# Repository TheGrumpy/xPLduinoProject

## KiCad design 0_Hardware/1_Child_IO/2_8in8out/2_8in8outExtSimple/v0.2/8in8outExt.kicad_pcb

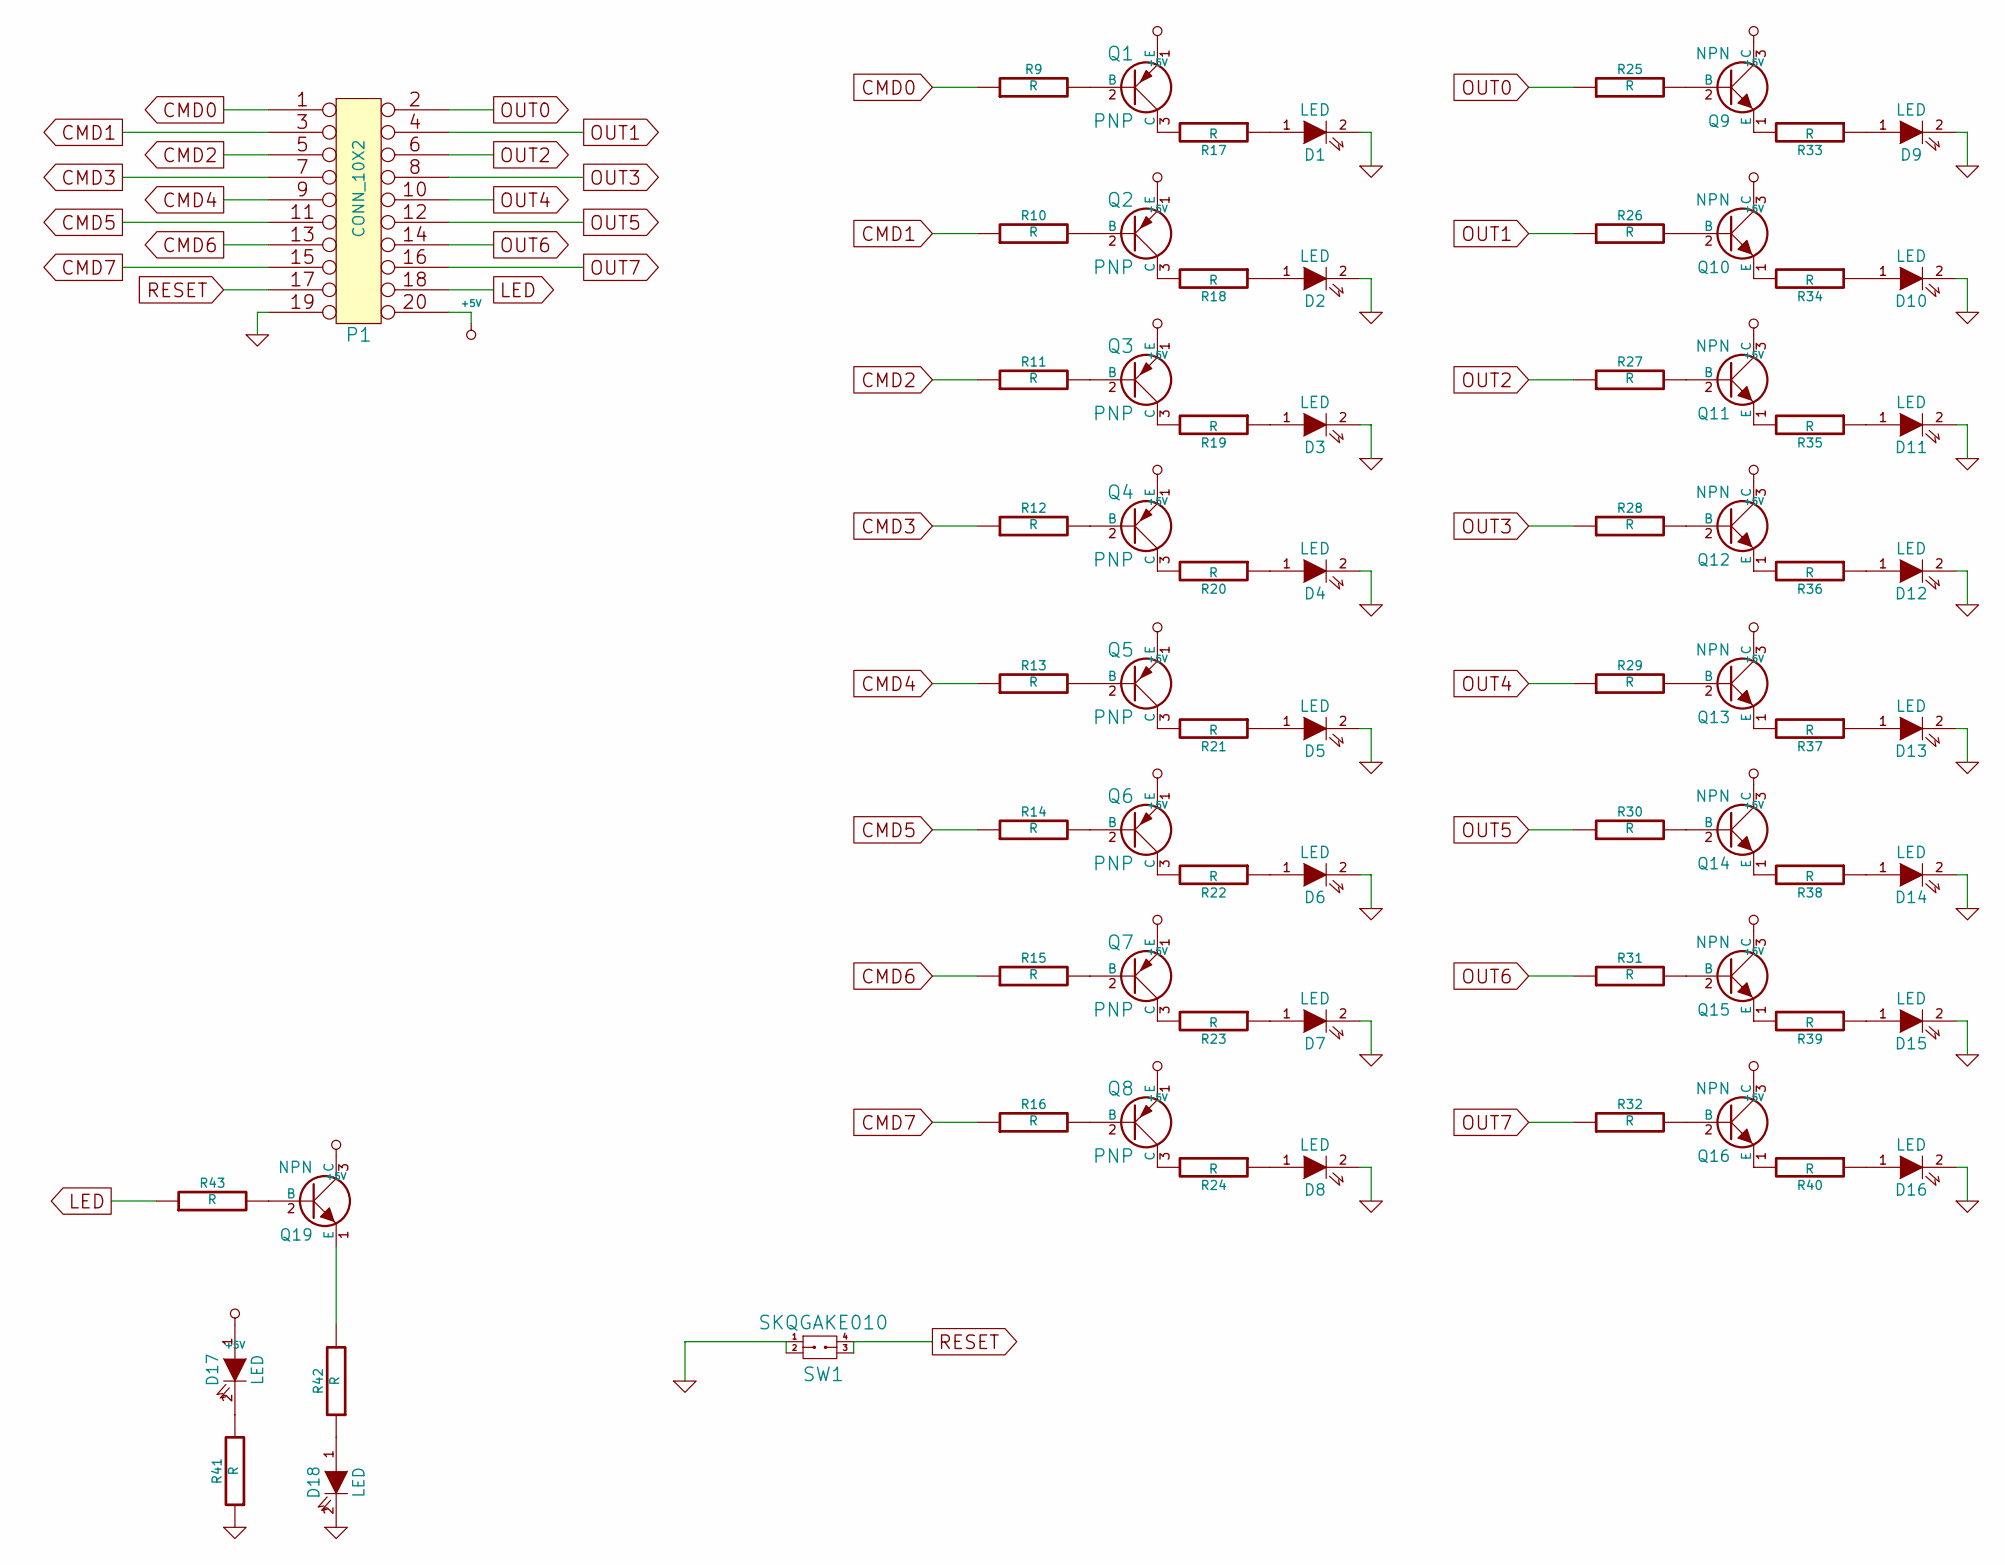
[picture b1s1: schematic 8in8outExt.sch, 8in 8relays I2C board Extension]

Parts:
D1, D2, D3, D4, D5, D6, D7, D8, D9, D10, D11, D12, D13, D14, D15, D16, D17, D18: LED
P1: CONN_10X2
Q1, Q2, Q3, Q4, Q5, Q6, Q7, Q8: PNP
Q9, Q10, Q11, Q12, Q13, Q14, Q15, Q16, Q19: NPN
R9, R10, R11, R12, R13, R14, R15, R16, R25, R26, R27, R28, R29, R30, R31, R32, R43: R
R17, R18, R19, R20, R21, R22, R23, R24, R33, R34, R35, R36, R37, R38, R39, R40, R41, R42: R
SW1: SKQGAKE010

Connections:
+5V: D17.1 (A), P1.20, Q1.1 (E), Q2.1 (E), Q3.1 (E), Q4.1 (E), Q5.1 (E), Q6.1 (E), Q7.1 (E), Q8.1 (E), Q9.3 (C), Q10.3 (C), Q11.3 (C), Q12.3 (C), Q13.3 (C), Q14.3 (C), Q15.3 (C), Q16.3 (C), Q19.3 (C)
CMD0: P1.1, R9.1
CMD1: P1.3, R10.1
CMD2: P1.5, R11.1
CMD3: P1.7, R12.1
CMD4: P1.9, R13.1
CMD5: P1.11, R14.1
CMD6: P1.13, R15.1
CMD7: P1.15, R16.1
GND: D1.2 (K), D2.2 (K), D3.2 (K), D4.2 (K), D5.2 (K), D6.2 (K), D7.2 (K), D8.2 (K), D9.2 (K), D10.2 (K), D11.2 (K), D12.2 (K), D13.2 (K), D14.2 (K), D15.2 (K), D16.2 (K), D18.2 (K), P1.19, R41.1, SW1.1, SW1.2
LED: P1.18, R43.1
unnamed: Q14.1 (E), R38.2
unnamed: Q14.2 (B), R30.2
unnamed: D14.1 (A), R38.1
unnamed: Q13.2 (B), R29.2
unnamed: Q13.1 (E), R37.2
unnamed: D13.1 (A), R37.1
unnamed: Q15.2 (B), R31.2
unnamed: Q16.1 (E), R40.2
unnamed: D16.1 (A), R40.1
unnamed: Q15.1 (E), R39.2
unnamed: D15.1 (A), R39.1
unnamed: D11.1 (A), R35.1
unnamed: Q10.2 (B), R26.2
unnamed: Q10.1 (E), R34.2
unnamed: Q11.1 (E), R35.2
unnamed: D10.1 (A), R34.1
unnamed: Q9.2 (B), R25.2
unnamed: Q9.1 (E), R33.2
unnamed: Q12.2 (B), R28.2
unnamed: Q12.1 (E), R36.2
unnamed: D12.1 (A), R36.1
unnamed: Q11.2 (B), R27.2
unnamed: Q19.1 (E), R42.2
unnamed: Q19.2 (B), R43.2
unnamed: Q16.2 (B), R32.2
unnamed: D18.1 (A), R42.1
unnamed: D17.2 (K), R41.2
unnamed: Q1.3 (C), R17.2
unnamed: D1.1 (A), R17.1
unnamed: Q2.3 (C), R18.2
unnamed: D2.1 (A), R18.1
unnamed: Q1.2 (B), R9.2
unnamed: Q6.3 (C), R22.2
unnamed: Q7.3 (C), R23.2
unnamed: D7.1 (A), R23.1
unnamed: Q6.2 (B), R14.2
unnamed: Q7.2 (B), R15.2
unnamed: D6.1 (A), R22.1
unnamed: Q5.2 (B), R13.2
unnamed: D9.1 (A), R33.1
unnamed: Q8.2 (B), R16.2
unnamed: Q8.3 (C), R24.2
unnamed: D8.1 (A), R24.1
unnamed: D3.1 (A), R19.1
unnamed: D4.1 (A), R20.1
unnamed: Q3.2 (B), R11.2
unnamed: Q3.3 (C), R19.2
unnamed: Q2.2 (B), R10.2
unnamed: Q4.2 (B), R12.2
unnamed: Q5.3 (C), R21.2
unnamed: D5.1 (A), R21.1
unnamed: Q4.3 (C), R20.2
OUT0: P1.2, R25.1
OUT1: P1.4, R26.1
OUT2: P1.6, R27.1
OUT3: P1.8, R28.1
OUT4: P1.10, R29.1
OUT5: P1.12, R30.1
OUT6: P1.14, R31.1
OUT7: P1.16, R32.1
RESET: P1.17, SW1.3, SW1.4

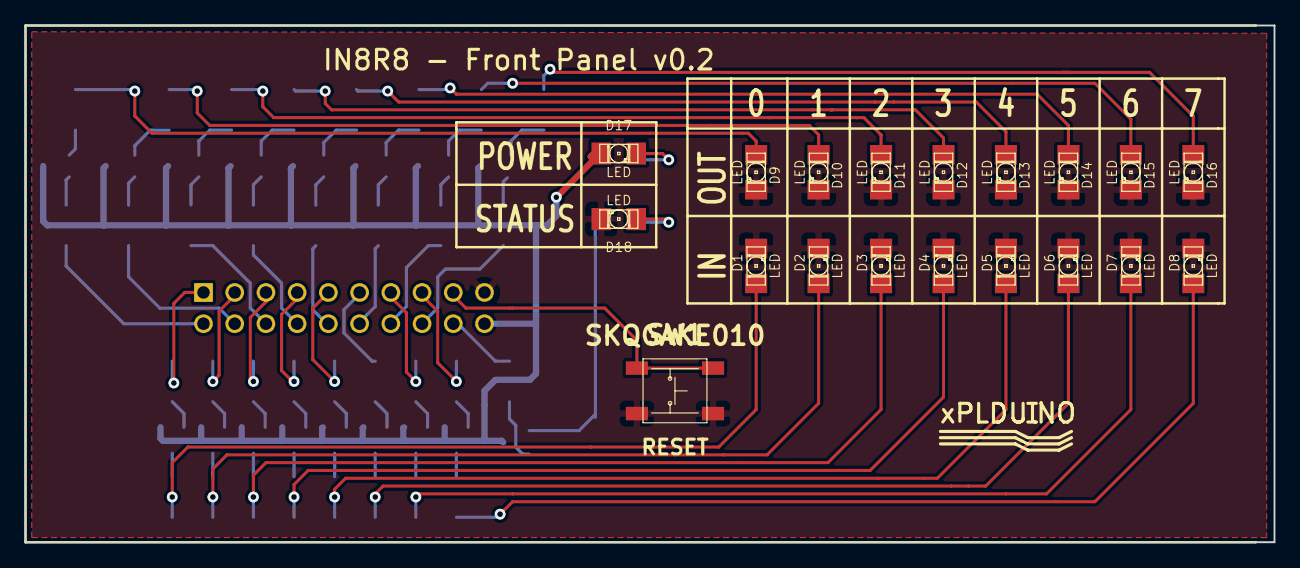
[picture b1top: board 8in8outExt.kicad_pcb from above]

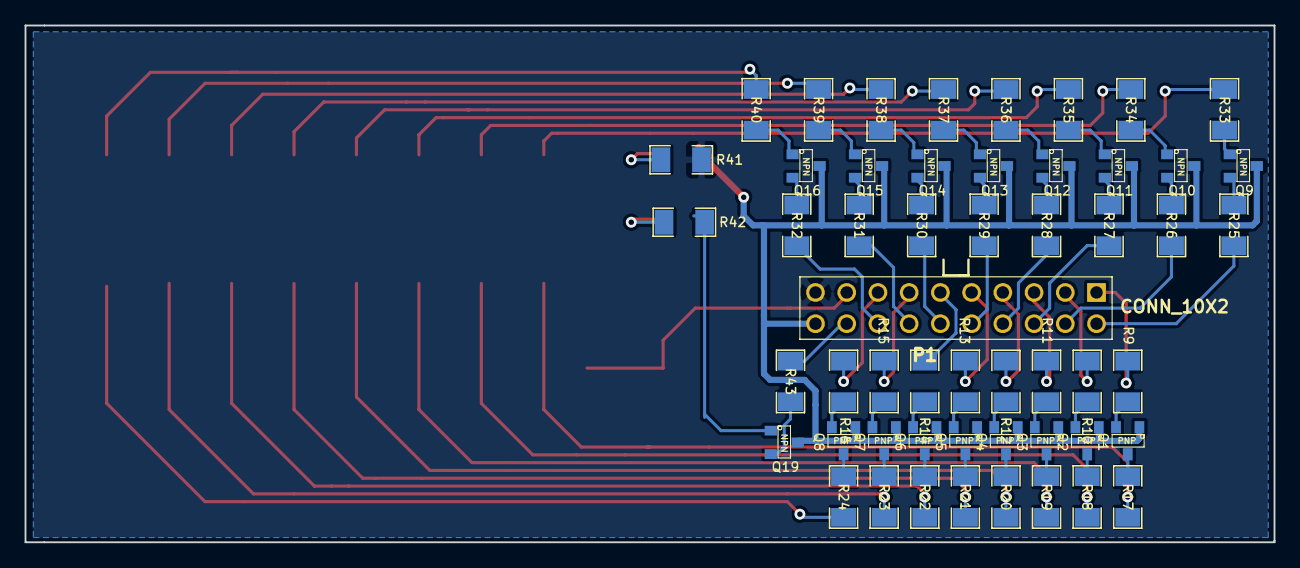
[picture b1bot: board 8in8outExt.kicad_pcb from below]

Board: 2 copper layers, 101.6 x 42.0 mm, 73 parts (53 on the bottom side), 72 nets.

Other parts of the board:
logo_xplduino: VAL**; logo_xplduino

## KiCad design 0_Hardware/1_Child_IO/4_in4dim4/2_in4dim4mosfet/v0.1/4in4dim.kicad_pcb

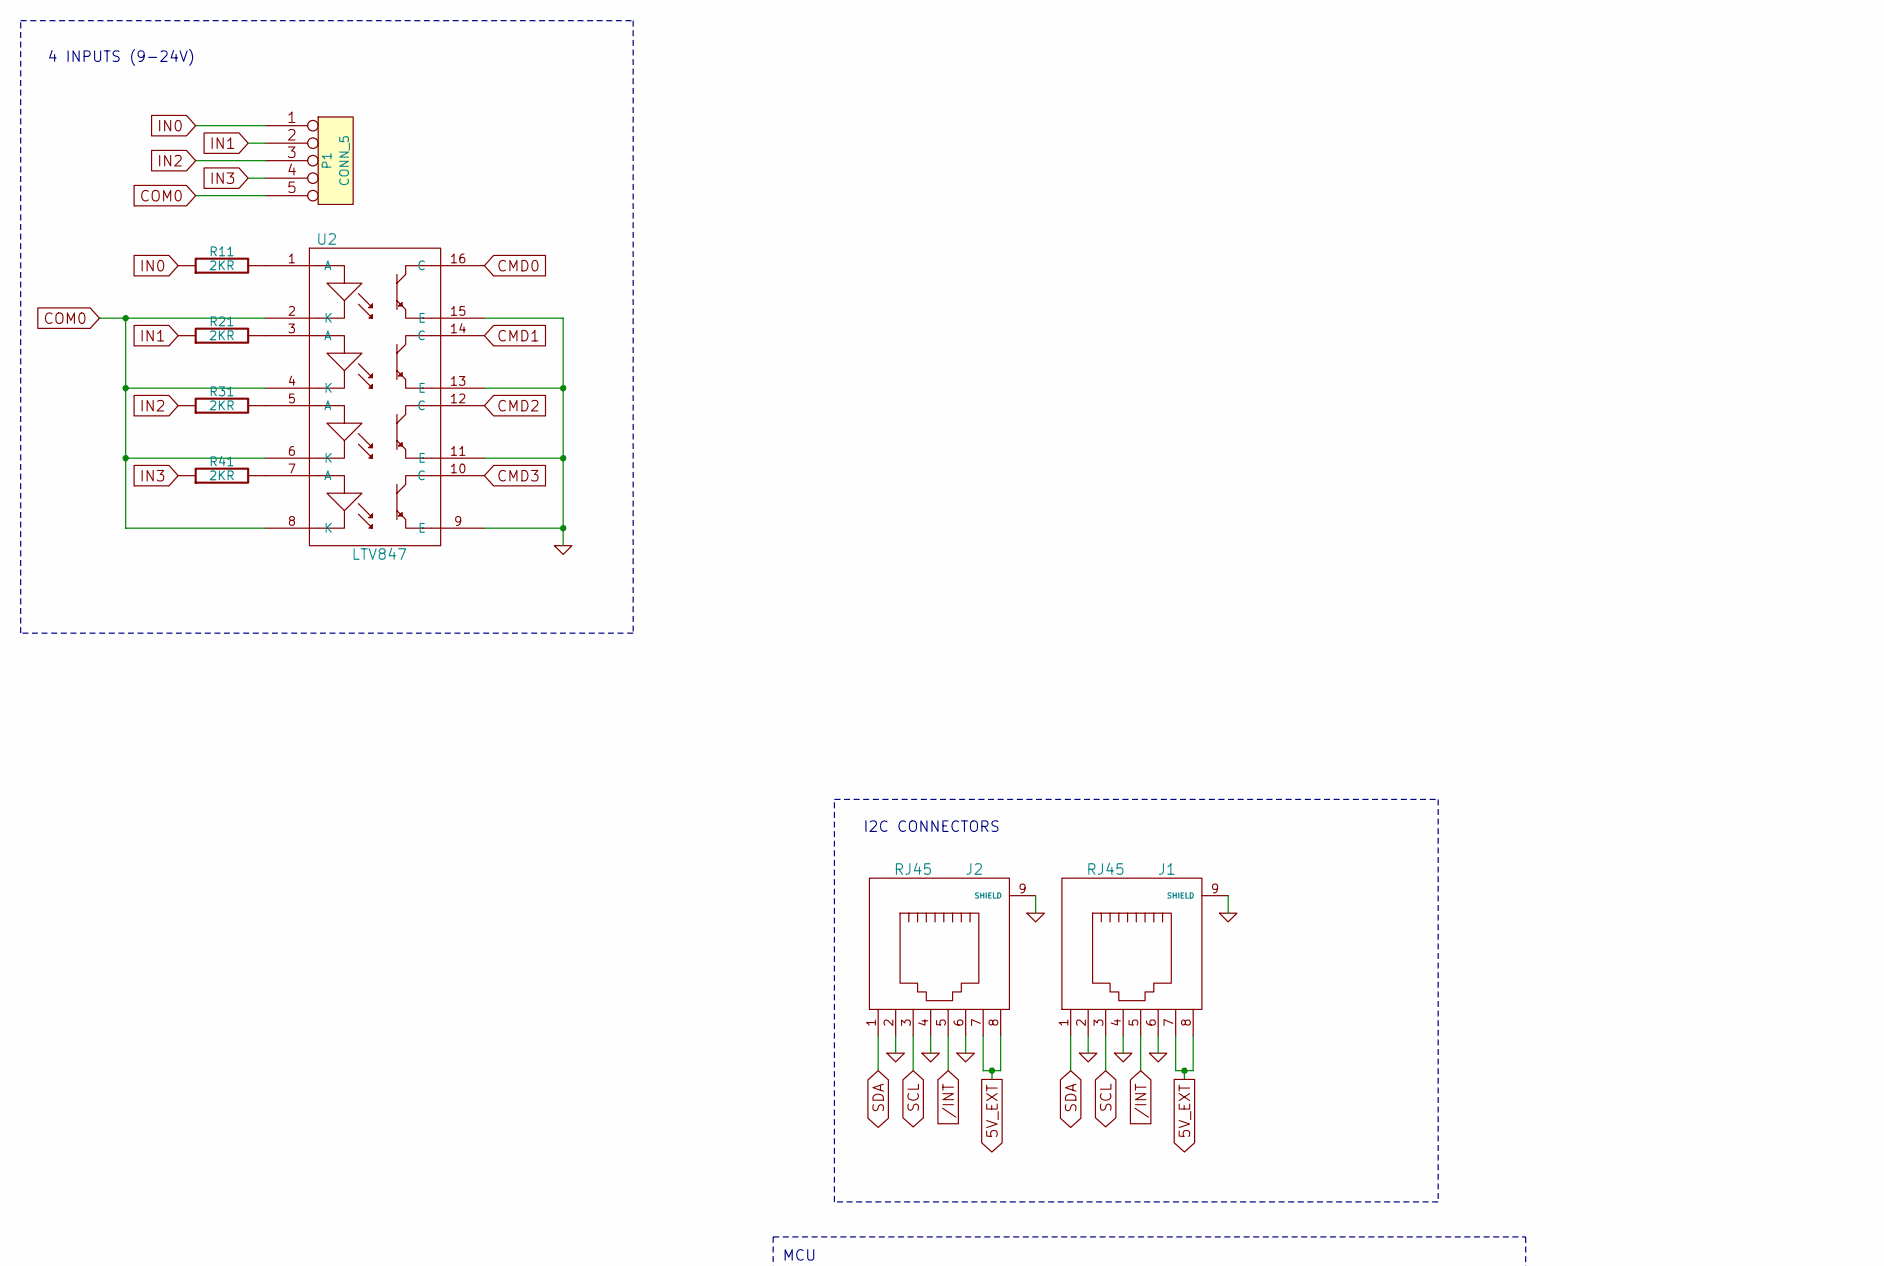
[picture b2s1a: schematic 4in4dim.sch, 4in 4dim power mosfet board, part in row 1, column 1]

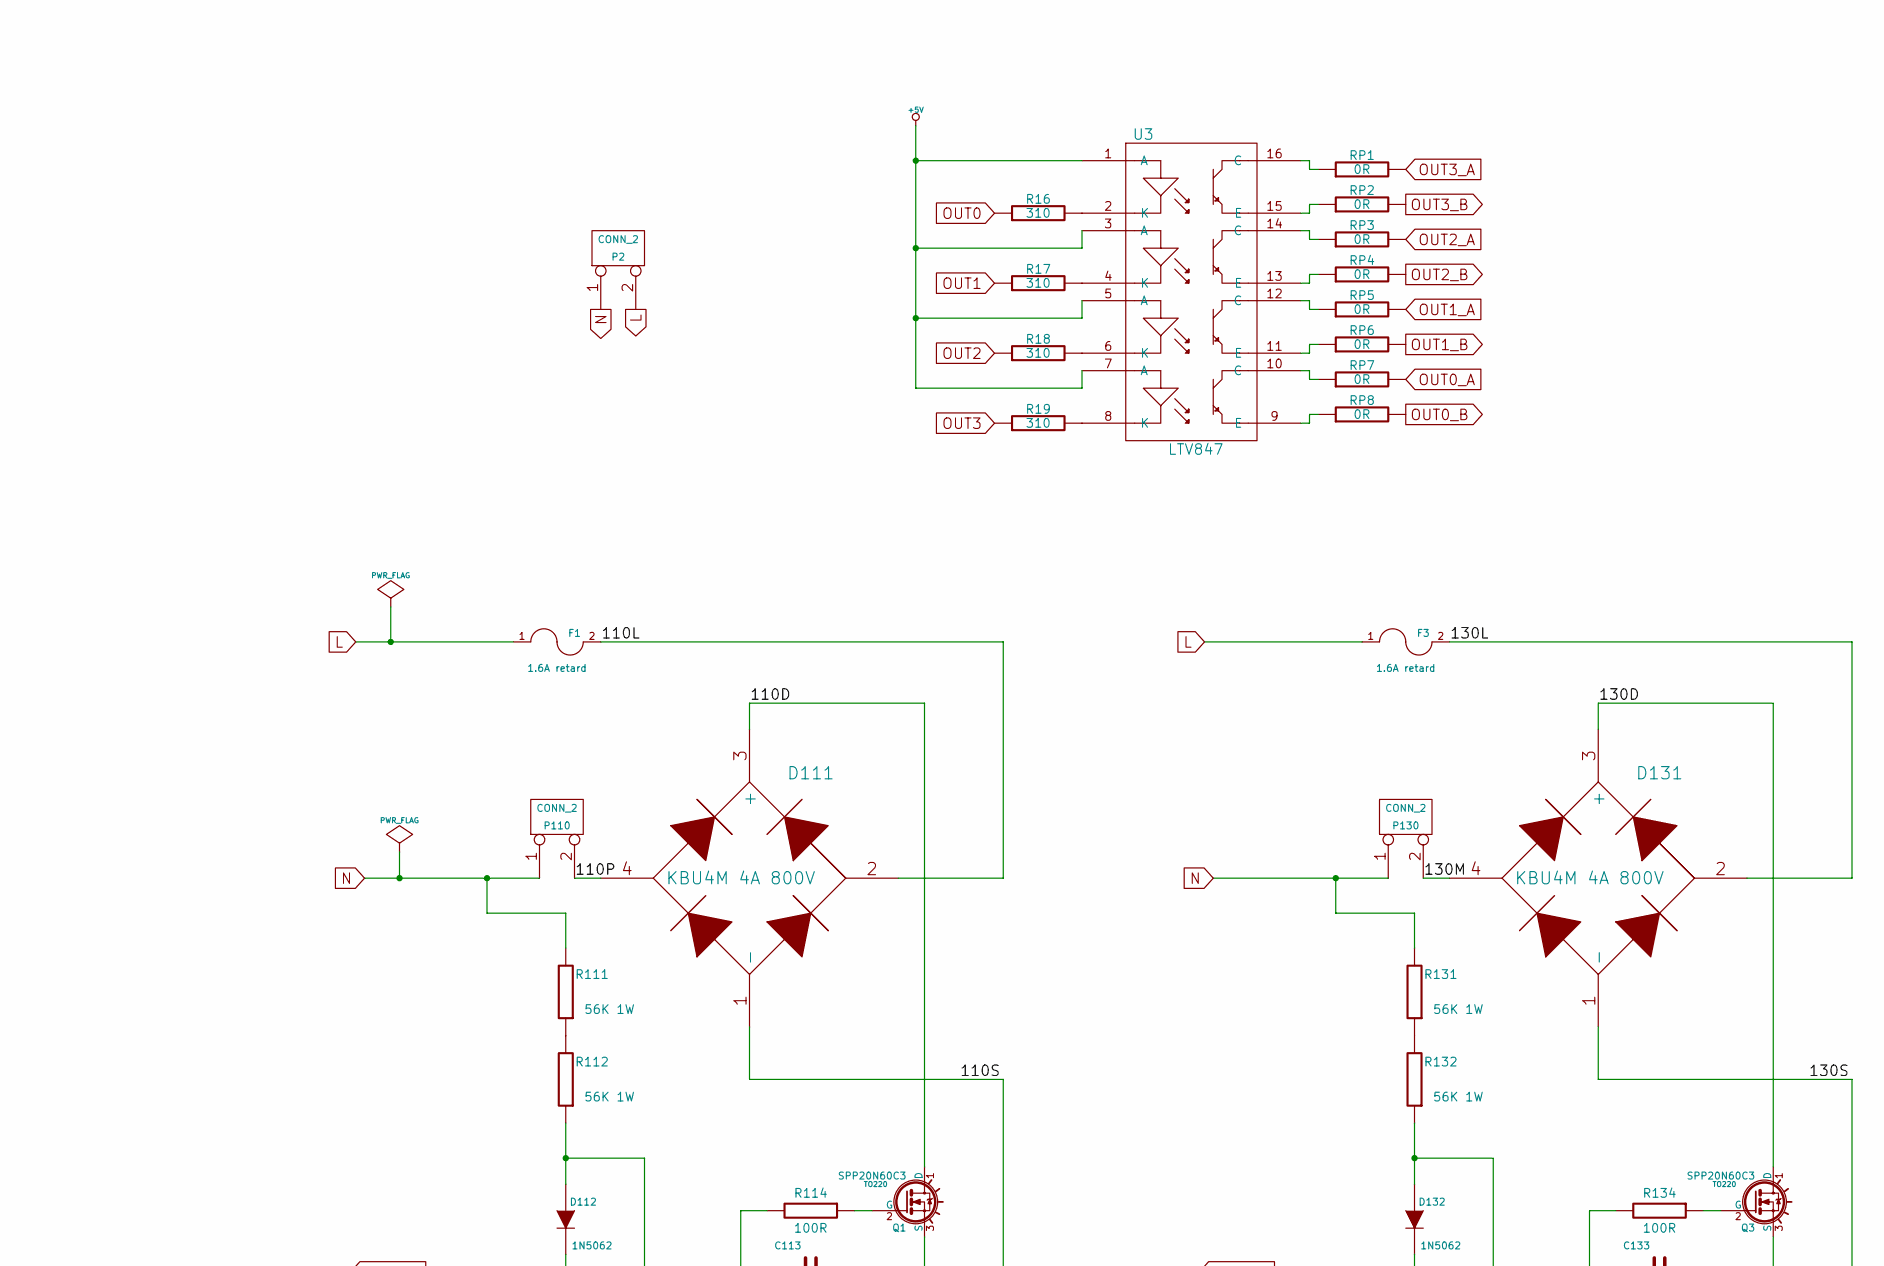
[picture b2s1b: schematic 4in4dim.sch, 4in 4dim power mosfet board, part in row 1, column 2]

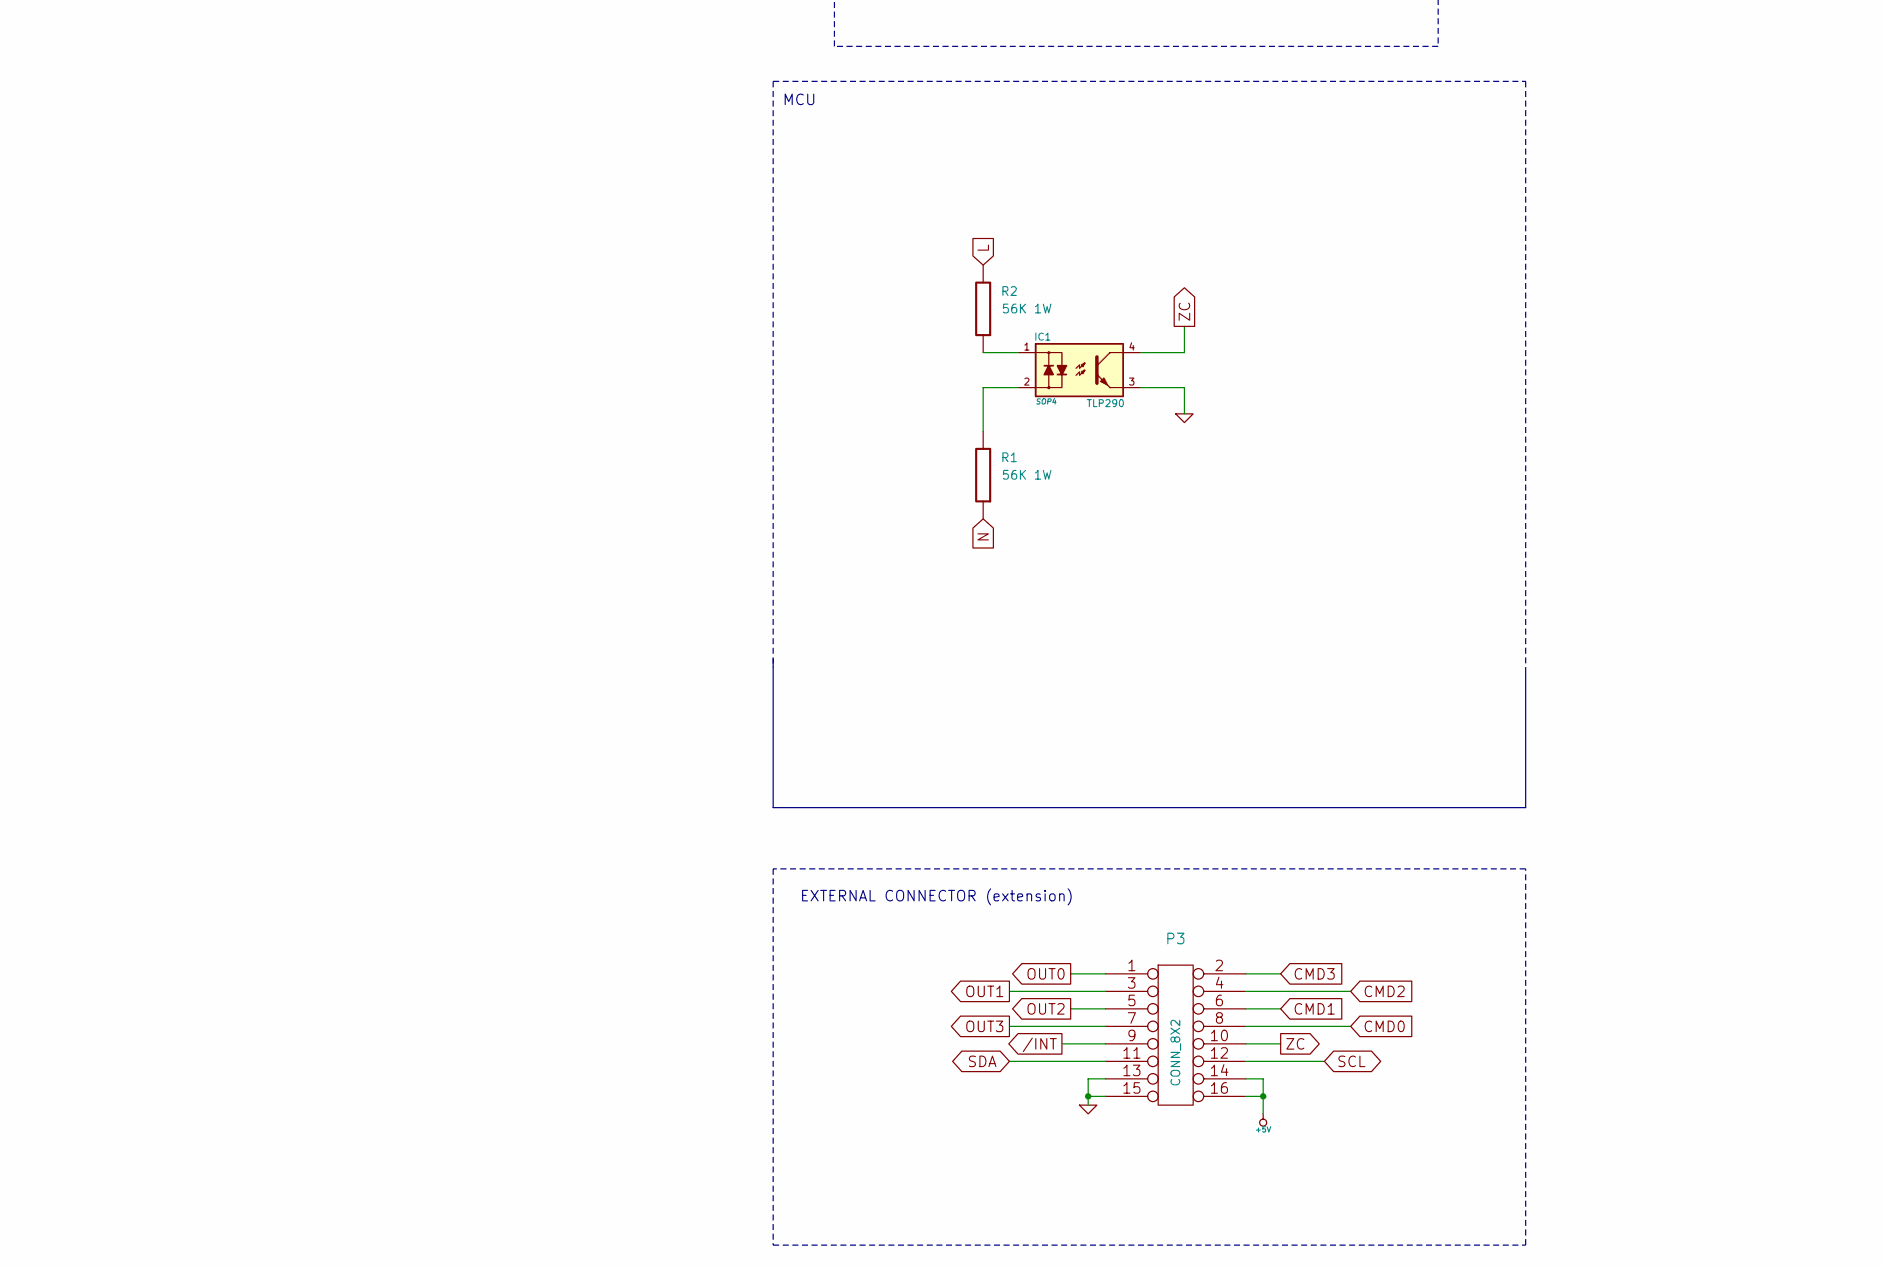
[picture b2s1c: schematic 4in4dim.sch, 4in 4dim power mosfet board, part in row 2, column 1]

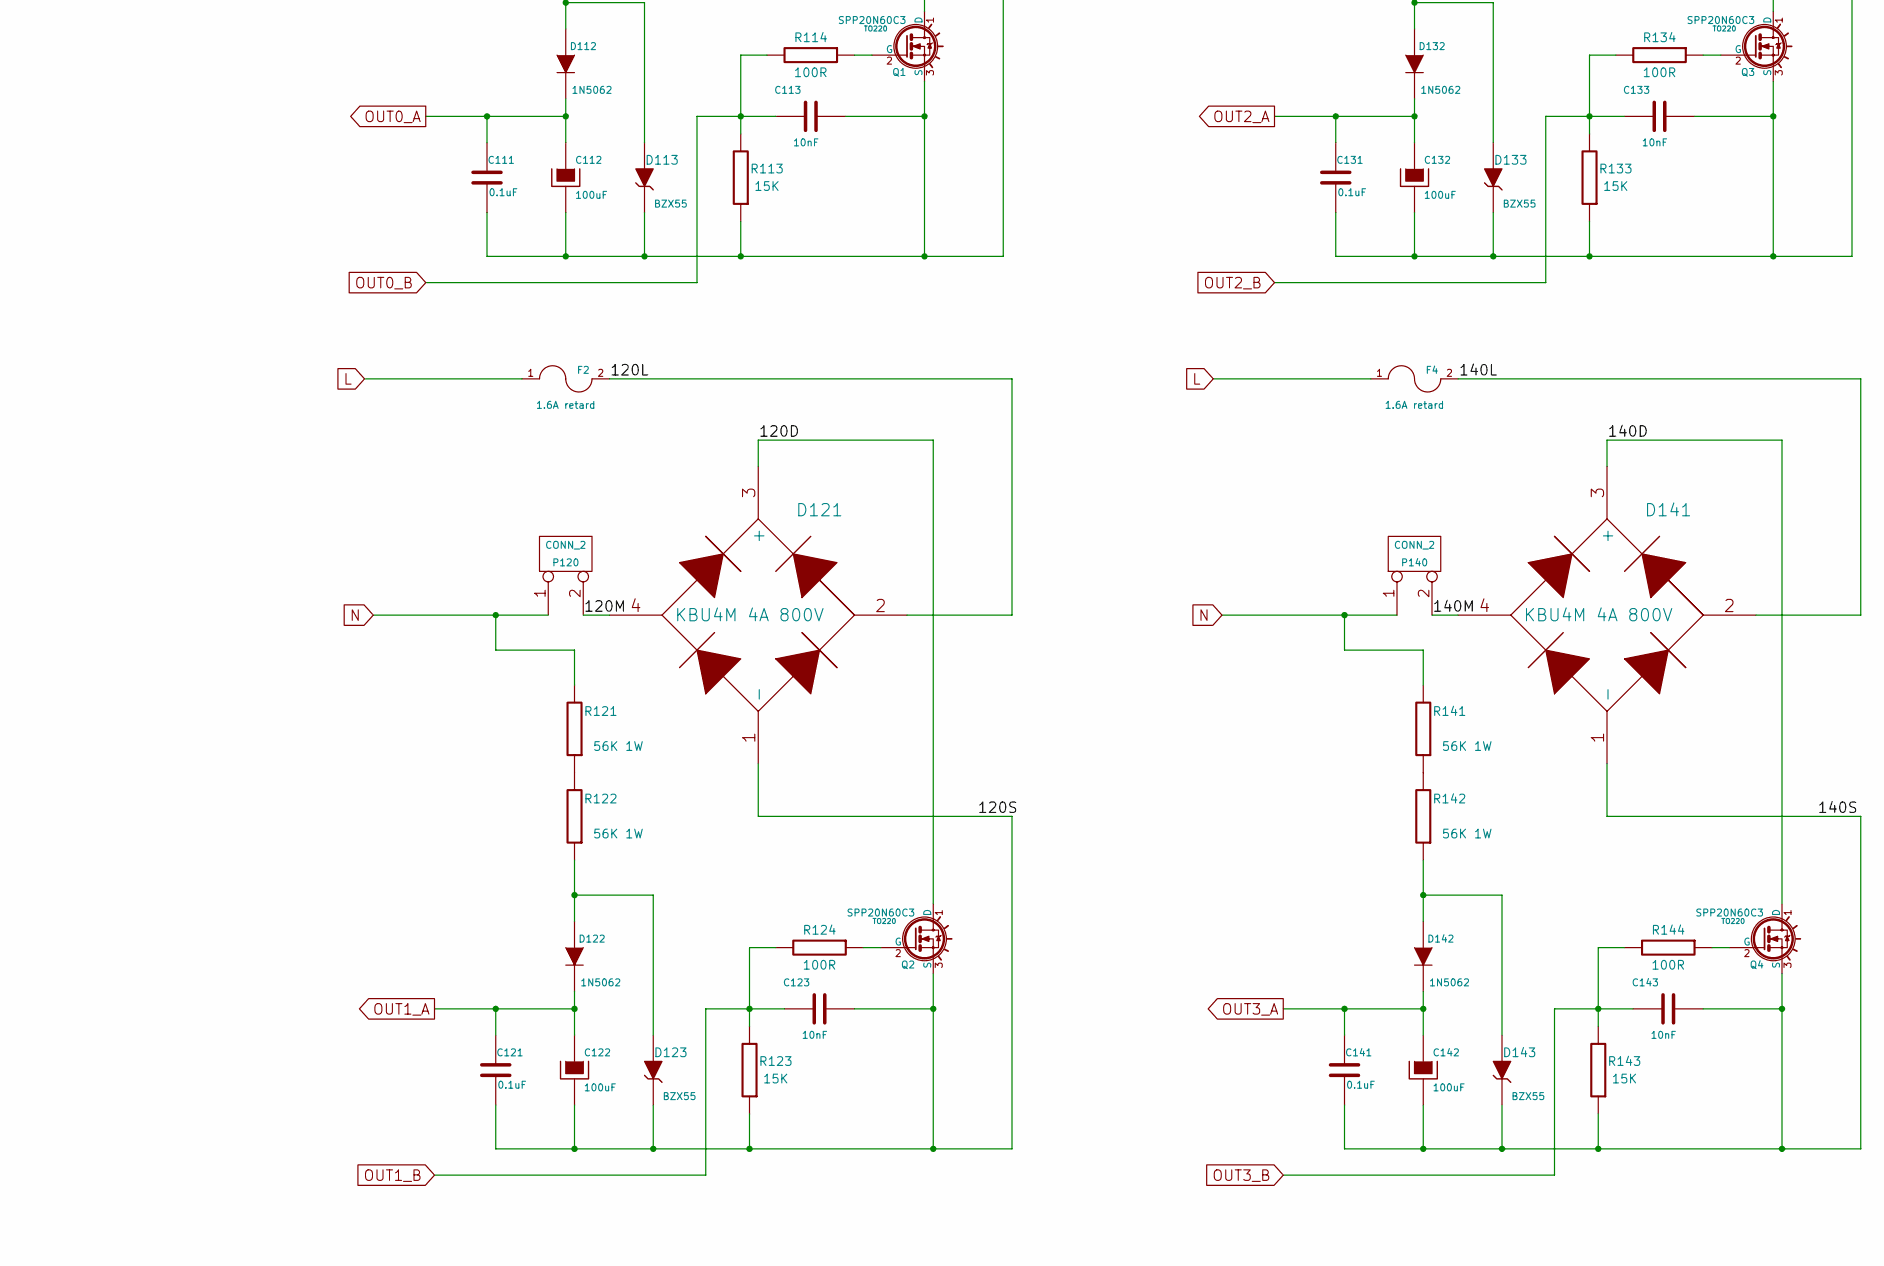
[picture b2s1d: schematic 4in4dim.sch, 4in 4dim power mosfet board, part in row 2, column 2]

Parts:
C111, C121, C131, C141: 0.1uF
C112, C122, C132, C142: 100uF
C113, C123, C133, C143: 10nF
D111, D121, D131, D141: KBU4M 4A 800V
D112, D122, D132, D142: 1N5062
D113, D123, D133, D143: BZX55
F1, F2, F3, F4: 1.6A retard
IC1: TLP290; SOP4
J1, J2: RJ45
P1: CONN_5
P2, P110, P120, P130, P140: CONN_2
P3: CONN_8X2
Q1, Q2, Q3, Q4: SPP20N60C3; TO220
R1, R2, R111, R112, R121, R122, R131, R132, R141, R142: 56K 1W
R11, R21, R31, R41: 2KR
R16, R17, R18, R19: 310
R113, R123, R133, R143: 15K
R114, R124, R134, R144: 100R
RP1, RP2, RP3, RP4, RP5, RP6, RP7, RP8: 0R
U2, U3: LTV847

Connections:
5V_EXT: J1.7, J1.8, J2.7, J2.8
+5V: P3.14, P3.16, U3.1 (A), U3.3 (A), U3.5 (A), U3.7 (A)
/110D: D111.3 (+), Q1.1 (D)
/110L: D111.2, F1.2
/110P: D111.4, P110.2 (PM)
/110S: C111.2, C112.2, C113.2, D111.1 (-), D113.2 (K), Q1.3 (S), R113.1
/120D: D121.3 (+), Q2.1 (D)
/120L: D121.2, F2.2
/120M: D121.4, P120.2 (PM)
/120S: C121.2, C122.2, C123.2, D121.1 (-), D123.2 (K), Q2.3 (S), R123.1
/130D: D131.3 (+), Q3.1 (D)
/130L: D131.2, F3.2
/130M: D131.4, P130.2 (PM)
/130S: C131.2, C132.2, C133.2, D131.1 (-), D133.2 (K), Q3.3 (S), R133.1
/140D: D141.3 (+), Q4.1 (D)
/140L: D141.2, F4.2
/140M: D141.4, P140.2 (PM)
/140S: C141.2, C142.2, C143.2, D141.1 (-), D143.2 (K), Q4.3 (S), R143.1
/INT: J1.5, J2.5, P3.9
CMD0: P3.8, U2.16 (C)
CMD1: P3.6, U2.14 (C)
CMD2: P3.4, U2.12 (C)
CMD3: P3.2, U2.10 (C)
COM0: P1.5, U2.2 (K), U2.4 (K), U2.6 (K), U2.8 (K)
GND: IC1.3, J1.2, J1.4, J1.6, J1.9 (SHIELD), J2.2, J2.4, J2.6, J2.9 (SHIELD), P3.13, P3.15, U2.9 (E), U2.11 (E), U2.13 (E), U2.15 (E)
IN0: P1.1, R11.1
IN1: P1.2, R21.1
IN2: P1.3, R31.1
IN3: P1.4, R41.1
L: F1.1, F2.1, F3.1, F4.1, P2.2 (PM), R2.2
N: P2.1, P110.1, P120.1, P130.1, P140.1, R1.1, R111.2, R121.2, R131.2, R141.2
unnamed: Q1.2 (G), R114.1
unnamed: D112.1 (A), D113.1 (A), R112.1
unnamed: RP8.1, U3.9 (E)
unnamed: RP7.1, U3.10 (C)
unnamed: RP3.1, U3.14 (C)
unnamed: RP2.1, U3.15 (E)
unnamed: RP1.1, U3.16 (C)
unnamed: RP4.1, U3.13 (E)
unnamed: RP6.1, U3.11 (E)
unnamed: RP5.1, U3.12 (C)
unnamed: IC1.2, R1.2
unnamed: IC1.1, R2.1
unnamed: Q4.2 (G), R144.1
unnamed: D142.1 (A), D143.1 (A), R142.1
unnamed: Q2.2 (G), R124.1
unnamed: D122.1 (A), D123.1 (A), R122.1
unnamed: Q3.2 (G), R134.1
unnamed: D132.1 (A), D133.1 (A), R132.1
unnamed: R16.2, U3.2 (K)
unnamed: R17.2, U3.4 (K)
unnamed: R18.2, U3.6 (K)
unnamed: R19.2, U3.8 (K)
unnamed: R11.2, U2.1 (A)
unnamed: R21.2, U2.3 (A)
unnamed: R31.2, U2.5 (A)
unnamed: R41.2, U2.7 (A)
unnamed: R111.1, R112.2
unnamed: R141.1, R142.2
unnamed: R121.1, R122.2
unnamed: R131.1, R132.2
OUT0: P3.1, R16.1
OUT0_A: C111.1, C112.1, D112.2 (K), RP7.2
OUT0_B: C113.1, R113.2, R114.2, RP8.2
OUT1: P3.3, R17.1
OUT1_A: C121.1, C122.1, D122.2 (K), RP5.2
OUT1_B: C123.1, R123.2, R124.2, RP6.2
OUT2: P3.5, R18.1
OUT2_A: C131.1, C132.1, D132.2 (K), RP3.2
OUT2_B: C133.1, R133.2, R134.2, RP4.2
OUT3: P3.7, R19.1
OUT3_A: C141.1, C142.1, D142.2 (K), RP1.2
OUT3_B: C143.1, R143.2, R144.2, RP2.2
SCL: J1.3, J2.3, P3.12
SDA: J1.1, J2.1, P3.11
ZC: IC1.4, P3.10

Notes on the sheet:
I2C CONNECTORS
MCU
4 INPUTS (9-24V)
EXTERNAL CONNECTOR (extension)

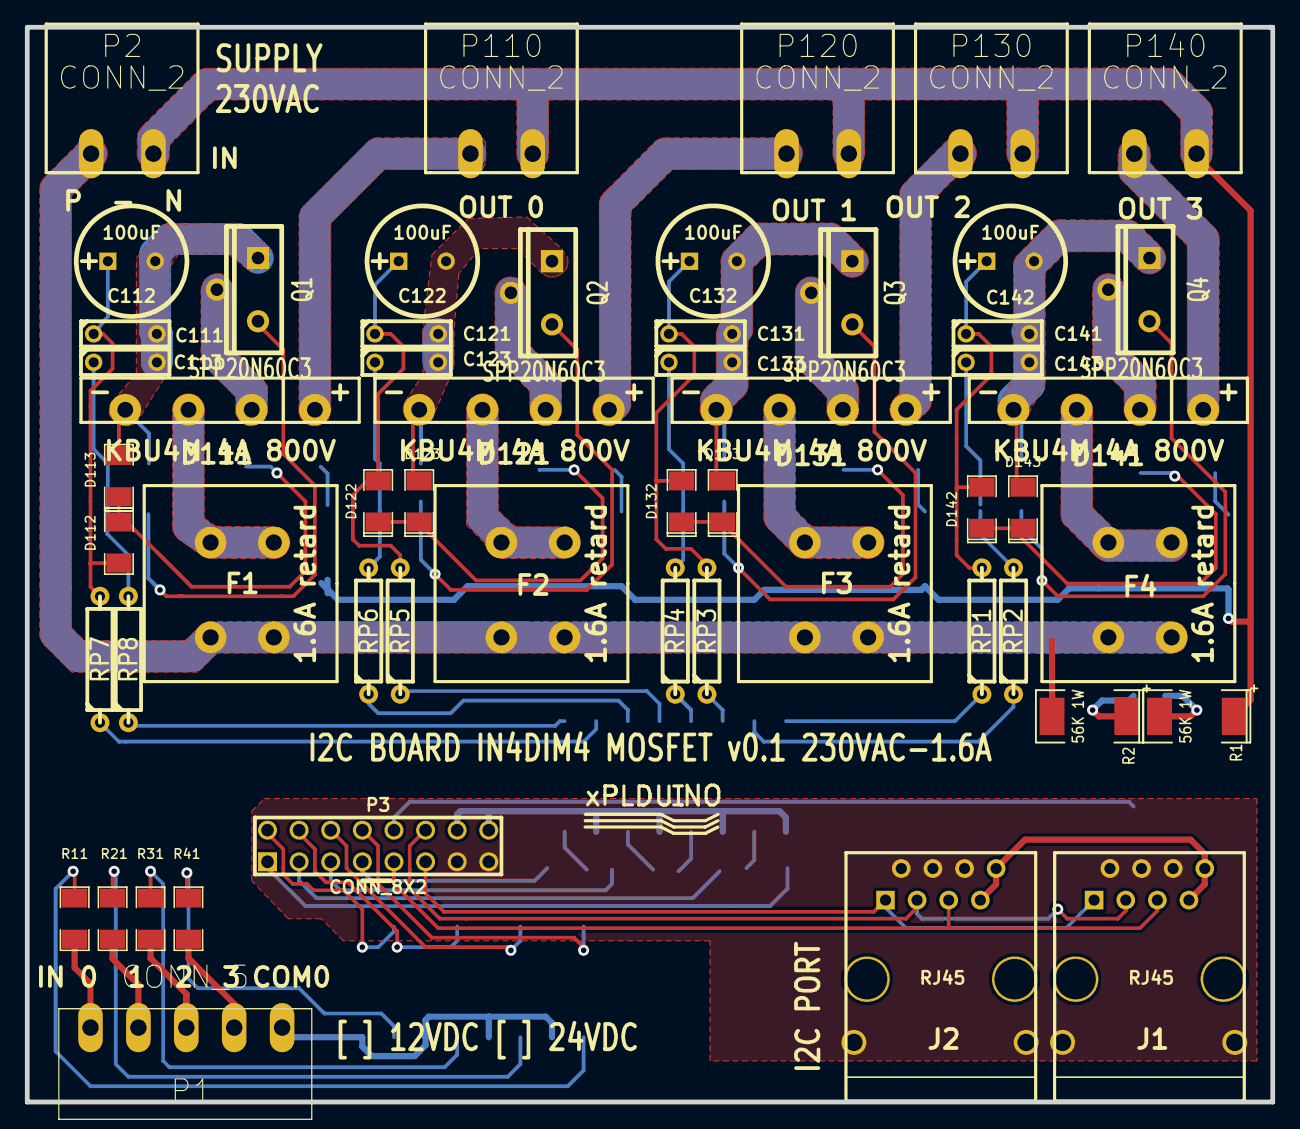
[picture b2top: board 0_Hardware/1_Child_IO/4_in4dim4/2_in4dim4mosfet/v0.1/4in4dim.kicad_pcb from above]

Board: 2 copper layers, 100.1 x 86.4 mm, 79 parts (0 on the bottom side), 76 nets.

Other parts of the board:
logo_xplduino: VAL**; logo_xplduino

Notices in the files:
0_Hardware/0_Mother/1_smb/v0.0/SMB.sch:
GNU GPL v2
